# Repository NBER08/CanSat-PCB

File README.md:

# A custom PCB for the 2026 Hungarian CanSat competition
This is the the design me and my team are working on this year. This is the second year that we try ourselves at this competition. Dispite last years sub-optimal results we are determined to give our everything. Our goal this year is to get to the finals and launch our CanSat.

## General architecture

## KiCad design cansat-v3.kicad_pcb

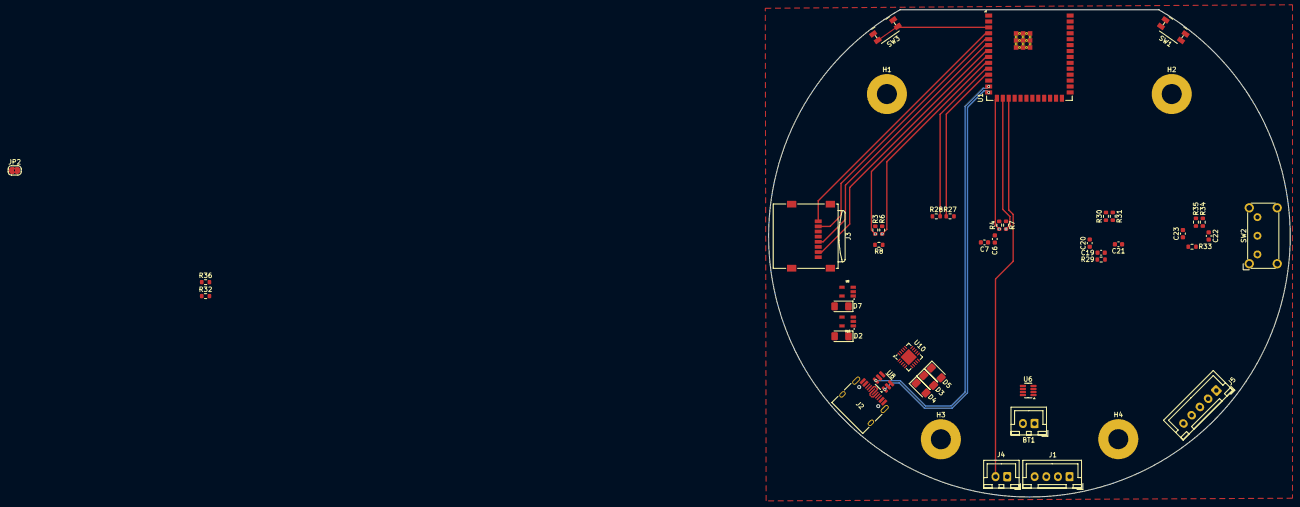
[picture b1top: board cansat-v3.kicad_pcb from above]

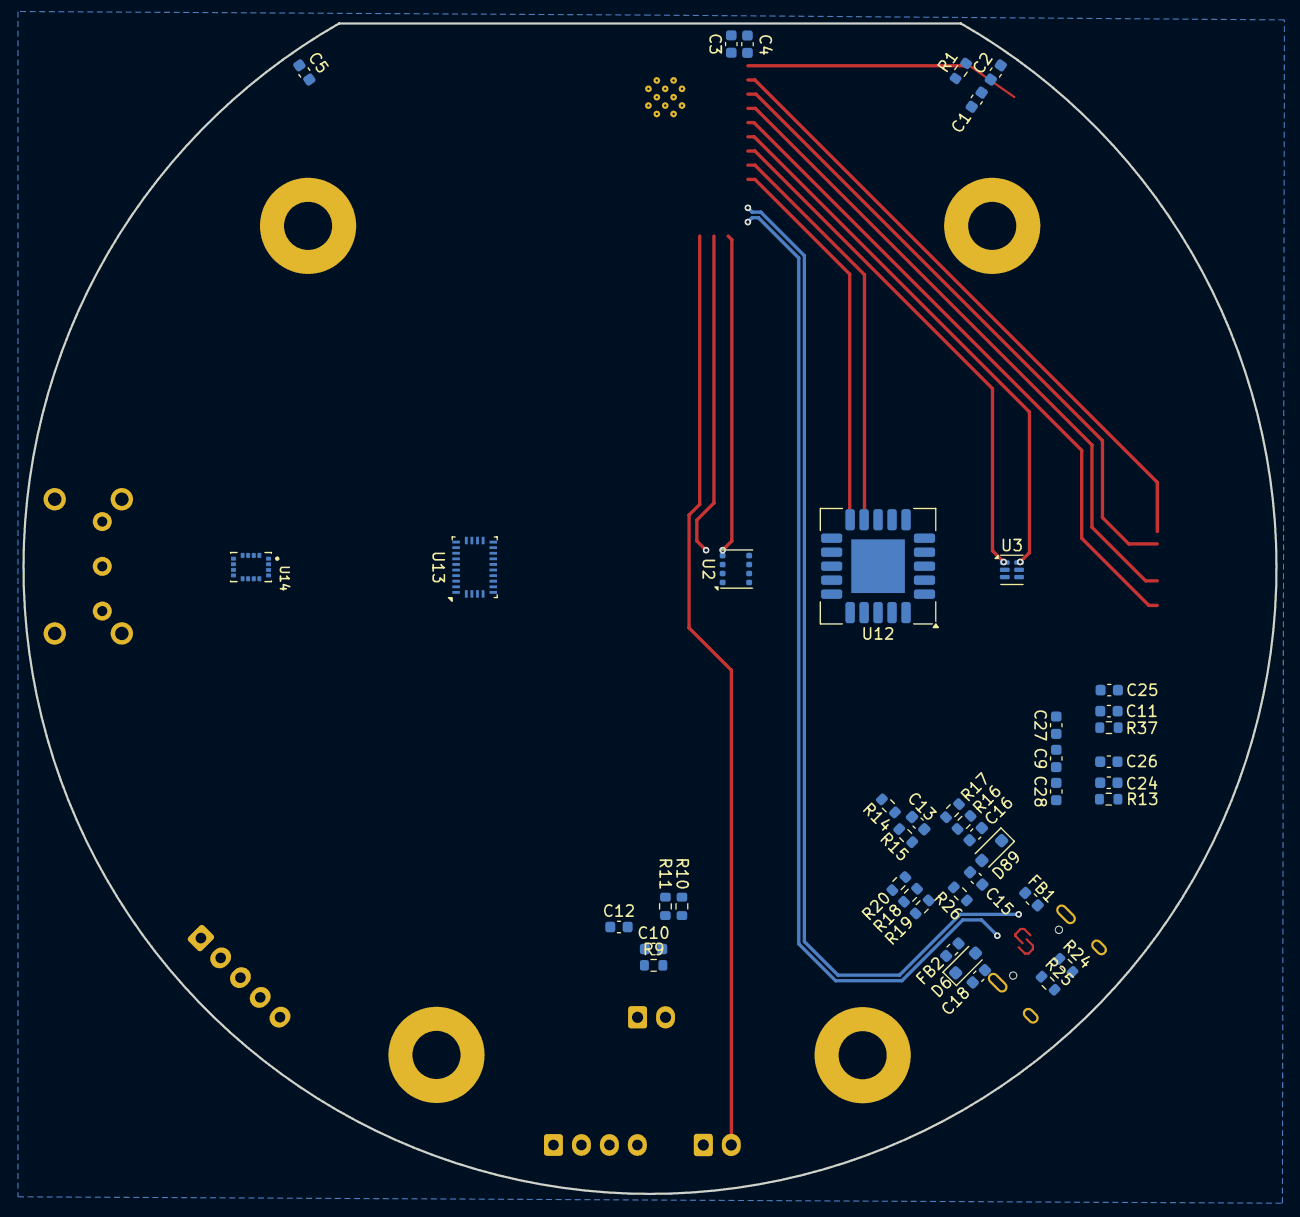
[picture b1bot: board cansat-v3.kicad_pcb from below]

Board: 4 copper layers, 112.0 x 104.6 mm, 90 parts (43 on the bottom side), 60 nets.

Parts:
BT1: Battery; JST_XH_B2B-XH-A_1x02_P2.50mm_Vertical
C1, C3, C5, C6, C7, C11, C12, C19, C22, C23, C24, C27, C28: 0.1u; C_0603_1608Metric
C2, C16: 10u; C_0603_1608Metric
C4: 22u; C_0603_1608Metric
C9: 470u; C_0603_1608Metric
C10, C20: 1u; C_0603_1608Metric
C13, C15: 4.7u; C_0603_1608Metric
C18: 100n; C_0603_1608Metric
C21: 0.12u; C_0603_1608Metric
C25, C26: 22n; C_0603_1608Metric
D2, D7: LED; LED_1206_3216Metric_Pad1.42x1.75mm_HandSolder
D3: Blue; LED_1206_3216Metric_Pad1.42x1.75mm_HandSolder
D4: Orange; LED_1206_3216Metric_Pad1.42x1.75mm_HandSolder
D5: Green; LED_1206_3216Metric_Pad1.42x1.75mm_HandSolder
D6: D_SOD-323_HandSoldering
D89: 1N5819; D_SOD-323_HandSoldering
FB1, FB2: LI0603G121R-10; L_0603_1608Metric
H1, H2, H3, H4: MountingHole_Pad; MountingHole_4.3mm_M4_Pad
J1: Conn_01x04_Socket; JST_XH_B4B-XH-A_1x04_P2.50mm_Vertical
J2: USB_C_Receptacle_USB2.0_16P; USB_C_Receptacle_HRO_TYPE-C-31-M-12
J3: Micro_SD_Card; microSD_HC_Wuerth_693072010801
J4: Conn_01x02_Socket; JST_XH_B2B-XH-A_1x02_P2.50mm_Vertical
J5: Conn_01x05_Socket; JST_XH_B5B-XH-A_1x05_P2.50mm_Vertical
JP2: SolderJumper_2_Bridged; SolderJumper-2_P1.3mm_Bridged2Bar_RoundedPad1.0x1.5mm
R1, R26, R27, R28, R29, R32, R36: 10k; R_0603_1608Metric
R3, R4, R6, R7, R8, R30, R31: 4.7k; R_0603_1608Metric
R9: 0.2; R_0603_1608Metric
R10, R11: 3.3k; R_0603_1608Metric
R13, R37: 66.5; R_0603_1608Metric
R14, R16: 2k; R_0603_1608Metric
R15: 1k; R_0603_1608Metric
R17: 2.4k; R_0603_1608Metric
R18: 68; R_0603_1608Metric
R19: 115; R_0603_1608Metric
R20: 100; R_0603_1608Metric
R24, R25: 5.1k; R_0603_1608Metric
R33: 3.3M; R_0603_1608Metric
R34, R35: 820; R_0603_1608Metric
SW1, SW3: SW_Push; Panasonic_EVQPUJ_EVQPUA
SW2: PWR; SW_E-Switch_EG1224_SPDT_Angled
U1: ESP32-S3-WROOM-2
U2: BME680; Bosch_LGA-8_3x3mm_P0.8mm_ClockwisePinNumbering
U3: TSL25911FN; AMS_TSL25911FN
U5: Analog PS; SOT94P279X129-5N
U6: INA219BxDCN; SOT-23-8
U8: SRV05-4; SOT-23-6_Handsoldering
U10: MCP73871; QFN-20-1EP_4x4mm_P0.5mm_EP2.5x2.5mm
U12: SCD40-D-R2; Sensirion_SCD4x-1EP_10.1x10.1mm_P1.25mm_EP4.8x4.8mm
U13: BNO055; LGA-28_5.2x3.8mm_P0.5mm
U14: AS7331-AQFM; PQFN50P365X260X119-16N
U15: Digital PS; SOT94P279X129-5N

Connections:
+3.3V: C3.1, C4.1, C6.1, C7.2, C12.2, C19.1, C22.1, C24.2, J1.1, J3.4 (VDD), J5.1, R1.1, R3.1, R4.2, R6.1, R7.2, R8.1, R10.1, R11.1, R13.1, R16.1, R27.1, R28.1, R29.1, R30.2, R31.2, R34.2, R35.2, U1.2 (3V3), U2.2 (CSB), U2.6 (VDDIO), U2.8 (VDD), U3.5 (VDD), U6.4 (VS), U10.4 (PROG2), U12.7 (VDD), U12.19 (VDD), U13.3 (VDD), U14.10 (VDDD), U15.5 (VOUT)
+5V: C16.1, D3.2 (A), D4.2 (A), D5.2 (A), FB1.2, U8.5 (VP), U10.2 (VPCC), U10.18 (IN), U10.19 (IN)
+BATT: BT1.1 (+), C10.1, C13.1, R9.1, SW2.1 (A), U6.1 (IN+), U10.14 (V_{BAT}), U10.15 (V_{BAT}), U10.16 (V_{BAT_SENSE})
/RST: C1.2, C2.1, R1.2, SW3.2, U1.3 (EN)
AS7331_SCL: R35.1, U1.33 (MTDO/IO40), U14.13 (SCL)
AS7331_SDA: R34.1, U1.34 (MTDI/IO41), U14.12 (SDA)
BME680_SCL: R4.1, U1.15 (IO3), U2.4 (SCK)
BME680_SDA: R7.1, U1.16 (IO46), U2.3 (SDI)
BNO055_RST: U1.23 (IO21), U13.11 (~RESET)
BNO055_SCL: R30.1, U1.31 (IO38), U13.19 (COM1)
BNO055_SDA: R31.1, U1.26 (IO45), U13.20 (COM0)
COMPASS_SCL: J4.2, U1.17 (IO9)
COMPASS_SDA: J4.1, U1.18 (IO10)
Earth: C18.1, D6.2 (A2), FB2.2, J2.A1 (GND), J2.A12 (GND), J2.B1 (GND), J2.B12 (GND), J2.S1 (SHIELD)
GND: BT1.2 (-), C1.1, C2.2, C3.2, C4.2, C5.1, C6.2, C7.1, C10.2, C11.1, C12.1, C13.2, C15.2, C16.2, C18.2, C19.2, C20.1, C21.1, C22.2, C24.1, C25.1, C26.1, C27.2, C28.1, D2.1 (K), D6.1 (A1), D7.1 (K), FB2.1, H1.1, H2.1, H3.1, H4.1, J1.2, J3.3 (CMD), J3.6 (VSS), J5.4, JP2.1 (A), R9.2, R14.2, R15.2, R17.2, R24.2, R25.2, R26.2, R32.2, R36.2, SW1.2, SW3.1, U1.1 (GND), U1.40 (GND), U1.41 (GND), U2.1 (GND), U2.5 (SDO), U2.7 (GND), U3.3 (GND), U5.2 (GND), U6.2 (IN-), U6.3 (GND), U6.7 (A0), U6.8 (A1), U8.2 (VN), U10.3 (SEL), U10.9 (~TE), U10.10 (V_{SS}), U10.11 (V_{SS}), U10.21 (V_{SS}), U12.6 (GND), U12.20 (GND), U12.21 (GND), U13.2 (GND), U13.5 (PS1), U13.6 (PS0), U13.17 (COM3), U13.18 (COM2), U13.25 (GNDIO), U14.11 (VSSD), U15.2 (GND)
GPS_RX: J1.3, U1.21 (IO13)
GPS_TX: J1.4, U1.22 (IO14)
INA219_SCL: R11.2, U1.20 (IO12), U6.5 (SCL)
INA219_SDA: R10.2, U1.19 (IO11), U6.6 (SDA)
LoRa_RST: J5.5, U1.32 (MTCK/IO39)
LoRa_RX: J5.3, U1.36 (RXD0/IO44)
LoRa_TX: J5.2, U1.37 (TXD0/IO43)
unnamed: D2.2 (A), R13.2
unnamed: D3.1 (K), R18.1
unnamed: D4.1 (K), R19.1
unnamed: D5.1 (K), R20.1
unnamed: D7.2 (A), R37.2
unnamed: C15.1, D89.2 (A), U10.1 (OUT), U10.20 (OUT)
unnamed: C9.1, C9.2, C27.1, C28.2, D89.1 (K), U5.1 (VIN), U15.1 (VIN)
unnamed: J2.A5 (CC1), R24.1
unnamed: J2.B5 (CC2), R25.1
unnamed: C5.2, SW1.1, U1.27 (IO0)
unnamed: R8.2, U3.2 (INT)
unnamed: C25.2, U5.4 (BP)
unnamed: R16.2, R17.1, U10.17 (CE)
unnamed: R14.1, U10.13 (PROG1)
unnamed: R15.1, U10.12 (PROG3)
unnamed: R20.2, U10.8 (STAT1/~LBO)
unnamed: R18.2, U10.7 (STAT2)
unnamed: R26.1, U10.5 (THERM)
unnamed: R19.2, U10.6 (~PG)
unnamed: C20.2, U13.9 (CAP)
unnamed: C21.2, U13.28 (VDDIO)
unnamed: R29.2, U13.4 (~BOOT_LOAD_PIN)
unnamed: R33.1, U14.4 (REXT)
unnamed: C26.2, U15.4 (BP)
PWR_EN: R32.1, R36.1, SW2.2 (B), U5.3 (EN), U15.3 (EN)
SCD40_SCL: R28.2, U1.10 (IO17), U12.9 (SCL)
SCD40_SDA: R27.2, U1.11 (IO18), U12.10 (SDA)
SD_CLK: J3.5 (CLK), U1.6 (IO6)
SD_CS: J3.1 (DAT2), U1.4 (IO4)
SD_MISO: J3.7 (DAT0), U1.7 (IO7)
SD_MOSI: J3.2 (DAT3/CD), U1.5 (IO5)
TSL2591_SCL: R6.2, U1.9 (IO16), U3.1 (SCL)
TSL2591_SDA: R3.2, U1.8 (IO15), U3.6 (SDA)
USB_D+: J2.A6 (D+), J2.B6 (D+), U1.14 (USB_D+/IO20), U8.1 (IO1)
USB_D-: J2.A7 (D-), J2.B7 (D-), U1.13 (USB_D-/IO19), U8.6 (IO4)
VBUS: FB1.1, J2.A4 (VBUS), J2.A9 (VBUS), J2.B4 (VBUS), J2.B9 (VBUS)
VDDA: C11.2, C23.1, R37.1, U5.5 (VOUT), U14.3 (VDDA)
VSSA: C23.2, JP2.2 (B), R33.2, U14.1 (VSSA), U14.2 (VSSA), U14.5 (VSSA), U14.6 (VSSA), U14.7 (A1), U14.14 (A0), U14.15 (VSSA), U14.16 (VSSA)

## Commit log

2025-09-25 new desktop first commit
2025-09-25 autopush test
2025-09-25 test
2025-09-26 Sensor development
2025-09-27 Power subsystem finished, Sensors continued
2025-09-28 Started layout
2025-09-29 Layout
2025-09-30 Component placement finished, started routing
